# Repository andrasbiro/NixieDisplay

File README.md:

# Nixie Display

This is my modular nixie display/clock.

It is designed around modules. Each module has:

- 2 nixie tube (with decimal point)
- preceiding colon
- shift register based cathode driver circuit
- any number of modules can be cascaded together

With my boards, the cathode drivers are sandwitched behind the main boards,

The control is based around a Wemos D1 mini and a small 170V power supply. It can also dim the tubes via PWM controlled optogate switching off the high voltage from the tubes.

The recommended input voltage is between 7.5V and 12V.

## Hardware

The PCB design is the most problematic part of the project. I'm proud of the small outline of the NixieBoards, but other than that, they are full with problems. For more details see [its own readme](./hardware/electronics/README.md).

3d printed case coming soon.

## Firmware

The firmware is written in platformIO.

### NixieLib

The nixie driver is written in its own library, what I called NixieLib, and is fully documented in its header file. It supports the following input formats:

- 2 digit number + 4 boolean for the 4 dots (decimal and colon) for each module
- Integer, right adjusted across all modules
- Fixed point number (float input, number of decimals in another input)

### Clock application

The clock gets the current time from NTP, converts it to local time (CET/CEST, modify the winter/summer variables for your timezone) and displays ont the tubes.

It also has OTA enabled and telnet based debugging.

## Future developement

These are the modifications I plan:

- 3d printed case
- simplify NTP/timezone, use ESP's time.h instead of libs
- MQTT support, so it can display anything from my home assistant
- BH1750fvi based dimming
- second display, using Z570M tubes

Otherwise, grab it and modify it to your heart's content, but I probably won't. Pull requests are welcome!

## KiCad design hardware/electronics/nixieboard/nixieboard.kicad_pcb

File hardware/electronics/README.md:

# PCBs for nixie modules

These are the PCBs for the modular nixie display I designed, *but note that they
have many problems*. I'm a firmware engineer and I hate working on PCBs, and
even though these have many problems (and I autorouted most of them, which seems
sacrilege in hw design), it reached the point where it is good enough for me.

Pull requests are welcome.

## The Nixie board

The Nixie board is designed around IN-12B nixies with INS-1 neon bulbs as colon.
When the colon is not populated, the pads of it can be hidden in the preceding
board. Therefor, the board can be used both as clock displays with a colon and
numerical displays.

It will likely work with thin legged standing style tubes too (like the GDR,
like Z570M).

This board also has 4 M3 mounting holes, in each corner (on a 36.5x29mm
rectangle)

The anode resistors should be tuned for the tubes and anode voltage, here's what
I used for IN-12B / INS-1 at 170V power supply:

- R1/R3: 12kOhm (main anode resistor)
- R2/R4: 91kOhm (additional resistor on the decimal point's cathode)
- R5/R6: 240kOhm (INS-1 anode resistor)

### Known issues

- The board includes a WS2812B ("neopixel") backlight for each tube but that
  never worked. However, I never really wanted to use it, just thought about
  maybe if it looks good, so I won't fix it.
- When used with TPIC6592 drivers, INS-1 needs an extra ~50V zener in series to
  allow it turn off. Since it is not socketed, it can be easily added.

## The Driver boards

The driver board fits under the nixie board and provides power/control to it. I
have two versions of it:

- Based on HV5122 (in socket)
- Based on TPIC6592 (smd)

I highliy recommend the one based on TPIC6592, as HV5122 does not have a true
latch (only output enable) and way more expensive.

Both design has footprint for filter caps, but I never used it on the TPIC
design.

The module connecting pin headers are ~15mm from each other when the nixie board
is used without colon, but I ended up using wires on one side and 90 degree pin
headers on the other. The excess wire can be tugged away between the boards.

### Known issues

- The 15mm distance was designed for pin headers measured for 14mm distance, but
  what I got in the end was much closer
- The HV5122 board is not very well tested. It was an earlier iteration of the
  design, but with a few hw errors, I managed to blew my chips, and I don't
  intend to order new ones.

## The Control board

**The control board has the most issues, and I strongly recommend against
manufacturing it before fixing it. However, I did fix it with ugly hacks, so I
won't bother paying for another run. I put it here for archiving only.**

The control board is designed around a Wemos D1 mini (or clone) and a
cheap/small 170V power supply, both readily available from aliexpress and
similar sites. It also has a pin header for I2C, where I have a bh1750fvi light
sensor panel connected for dimming.

### Known issues

- I missed routing the 12V input to anything - fixable with a jumper wire
- AMS1117 was a bad decision for running the Wemos, and every other 5V device. I
  currently have a 3 pin DCDC board wired to its pads
- I used an optogate for dimming (via PWM) the high voltage. My driver board has
  a shutdown pin that would have probably work just as good
- The level shifters are configured for 12V (HV5122), and needs cutting a
  trace/adding a jumper wire to set it for 5V, needed for the TPIC drivers
- The power input needs bigger holes on the PCB to be able to use with proper
  wire gauge.

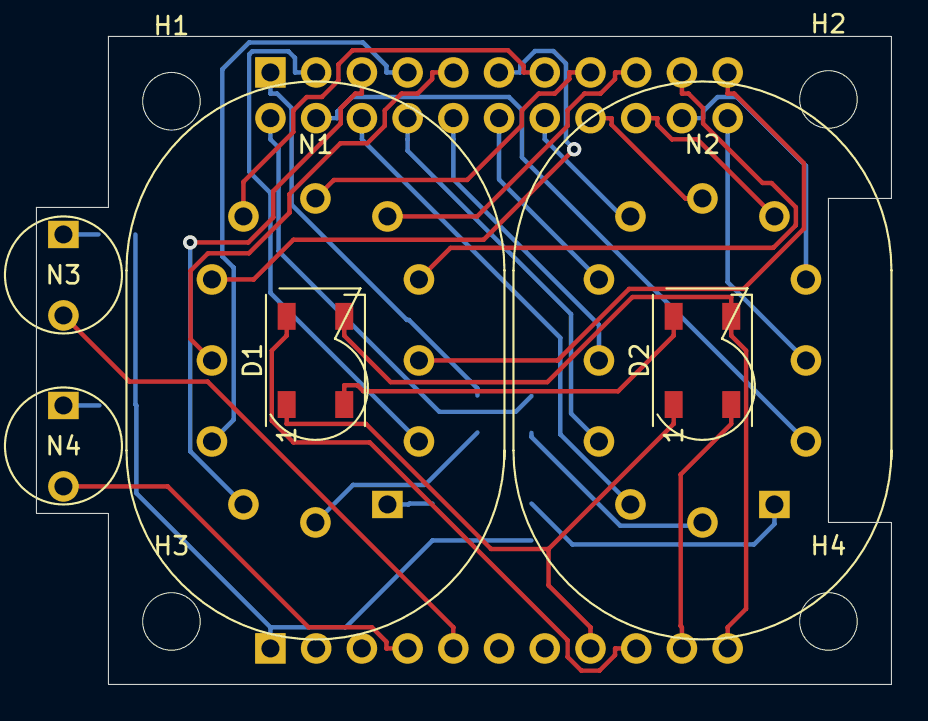
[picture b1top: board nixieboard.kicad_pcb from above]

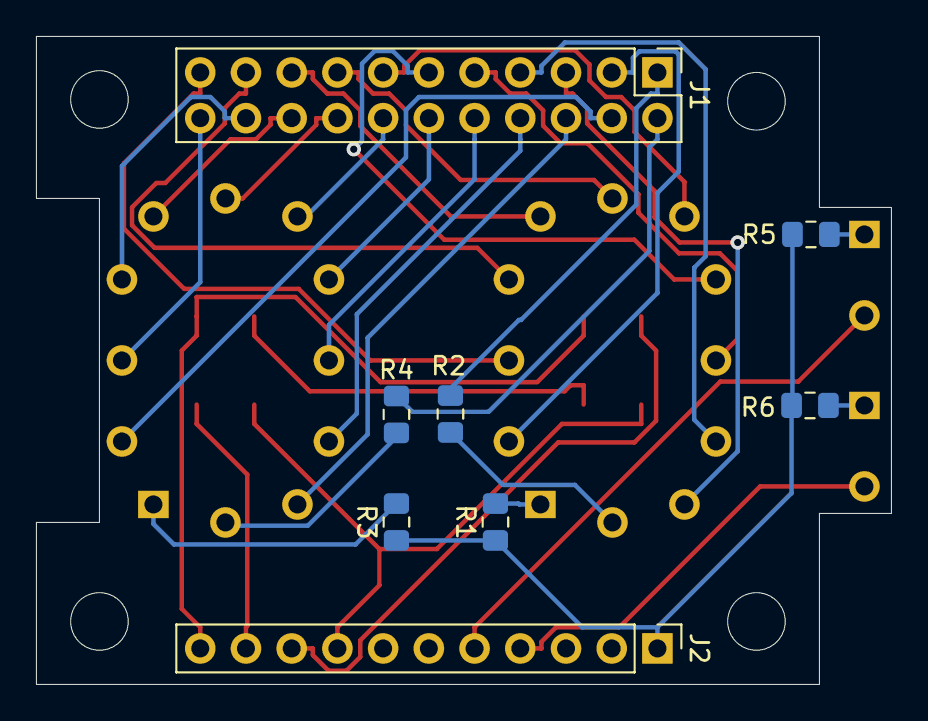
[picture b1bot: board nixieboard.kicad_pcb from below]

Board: 2 copper layers, 47.5 x 36.0 mm, 18 parts (8 on the bottom side), 36 nets.

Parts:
D1, D2: WS2812B; LED_WS2812B_PLCC4_5.0x5.0mm_P3.2mm
H1, H2, H3, H4: MountingHole; MountingHole_3.2mm_M3
J1: Cathodes; PinHeader_2x11_P2.54mm_Vertical
J2: PowerMisc; PinHeader_1x11_P2.54mm_Vertical
N1, N2: IN12B; in12b_pinsocket
N3, N4: INS-1; ins-1
R1, R3: 68k; R_0805_2012Metric_Pad1.15x1.40mm_HandSolder
R2, R4: 500k; R_0805_2012Metric_Pad1.15x1.40mm_HandSolder
R5, R6: 220k; R_0805_2012Metric_Pad1.15x1.40mm_HandSolder

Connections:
+5V: D1.1, D2.1, J2.8
GND: D1.3, D2.3, J2.11
HT: J2.1, R1.1, R3.1, R5.1, R6.1
unnamed: D1.2, D2.4
unnamed: D1.4, J2.9
unnamed: D2.2, J2.10
unnamed: J1.1, R2.2
unnamed: J1.2, R4.2
unnamed: J1.3, N1.2
unnamed: J1.4, N2.2
unnamed: J1.5, N1.11
unnamed: J1.6, N2.11
unnamed: J1.7, N1.10
unnamed: J1.8, N2.10
unnamed: J1.9, N1.9
unnamed: J1.10, N2.9
unnamed: J1.11, N1.8
unnamed: J1.12, N2.8
unnamed: J1.13, N1.7
unnamed: J1.14, N2.7
unnamed: J1.15, N1.6
unnamed: J1.16, N2.6
unnamed: J1.17, N1.5
unnamed: J1.18, N2.5
unnamed: J1.19, N1.4
unnamed: J1.20, N2.4
unnamed: J1.21, N1.3
unnamed: J1.22, N2.3
unnamed: J2.4, N4.2
unnamed: J2.5, N3.2
unnamed: N1.1, R1.2
unnamed: N1.12, R2.1
unnamed: N2.1, R3.2
unnamed: N2.12, R4.1
unnamed: N3.1, R5.2
unnamed: N4.1, R6.2

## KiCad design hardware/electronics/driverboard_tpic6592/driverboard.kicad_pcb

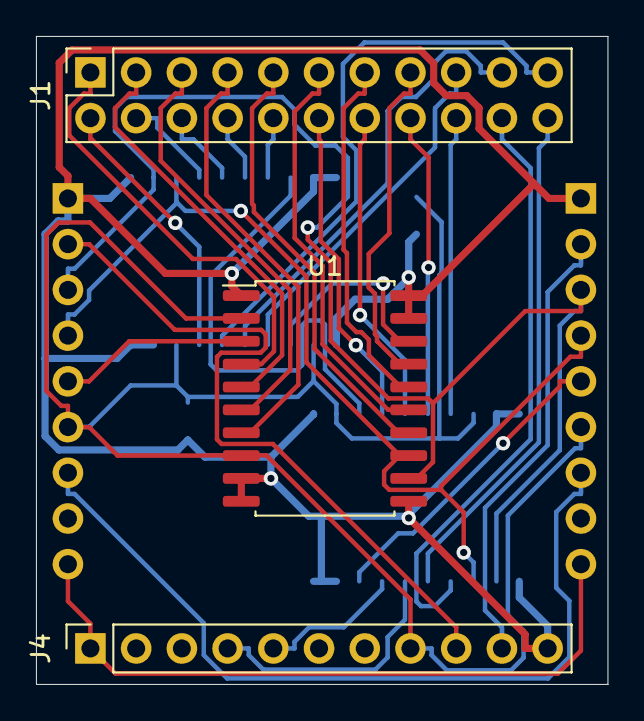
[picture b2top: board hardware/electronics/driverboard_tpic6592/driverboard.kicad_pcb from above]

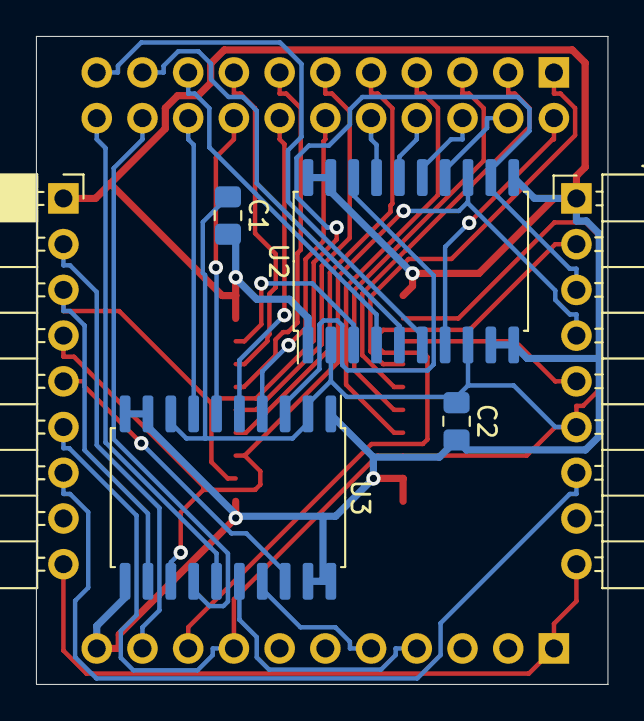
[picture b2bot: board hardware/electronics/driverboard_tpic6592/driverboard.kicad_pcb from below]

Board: 2 copper layers, 31.8 x 36.0 mm, 9 parts (6 on the bottom side), 36 nets.

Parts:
C1: C; C_0805_2012Metric_Pad1.18x1.45mm_HandSolder
C2: CP; C_0805_2012Metric_Pad1.18x1.45mm_HandSolder
J1: Cathodes; PinSocket_2x11_P2.54mm_Vertical
J2: In; PinHeader_1x09_P2.54mm_Horizontal
J3: Out; PinSocket_1x09_P2.54mm_Horizontal
J4: PowerMisc; PinSocket_1x11_P2.54mm_Vertical
U1, U2, U3: TPIC6595; SOIC-20W_7.5x12.8mm_P1.27mm

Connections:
+5V: C1.1, C2.1, J2.6, J3.6, J4.8, U1.2, U1.8, U2.2, U2.8, U3.2, U3.8
+12V: J2.7, J3.7
GND: C1.2, C2.2, J2.1, J3.1, J4.11, U1.1, U1.9, U1.10, U1.11, U1.19, U1.20, U2.1, U2.9, U2.10, U2.11, U2.19, U2.20, U3.1, U3.9, U3.10, U3.11, U3.19, U3.20
HT: J2.9, J3.9, J4.1
unnamed: J1.1, U1.4
unnamed: J1.2, U2.7
unnamed: J1.3, U1.5
unnamed: J1.4, U2.14
unnamed: J1.5, U1.6
unnamed: J1.6, U2.15
unnamed: J1.7, U1.7
unnamed: J1.8, U2.16
unnamed: J1.9, U1.14
unnamed: J1.10, U2.17
unnamed: J1.11, U1.15
unnamed: J1.12, U3.4
unnamed: J1.13, U1.16
unnamed: J1.14, U3.5
unnamed: J1.15, U1.17
unnamed: J1.16, U3.6
unnamed: J1.17, U2.4
unnamed: J1.18, U3.7
unnamed: J1.19, U2.5
unnamed: J1.20, U3.14
unnamed: J1.21, U2.6
unnamed: J1.22, U3.15
unnamed: J2.2, J4.9
unnamed: J2.3, J3.3, U1.12, U2.12, U3.12
unnamed: J2.4, J3.4, U1.13, U2.13, U3.13
unnamed: J2.5, U1.3
unnamed: J3.2, J4.10
unnamed: J3.5, U3.18
unnamed: J4.4, U3.16
unnamed: J4.5, U3.17
unnamed: U1.18, U2.3
unnamed: U2.18, U3.3

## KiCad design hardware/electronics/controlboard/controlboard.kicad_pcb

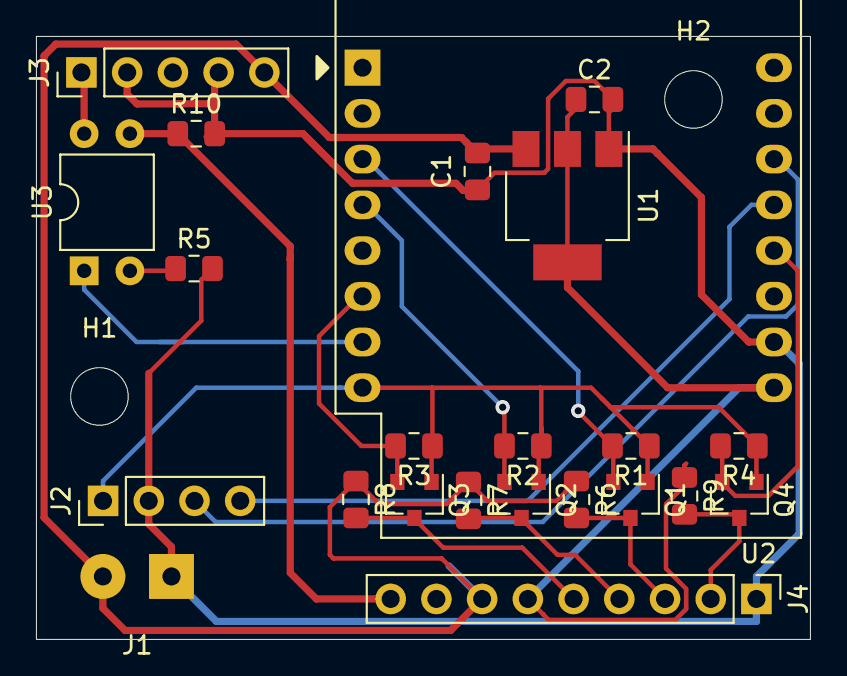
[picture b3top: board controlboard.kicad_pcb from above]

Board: 2 copper layers, 43.0 x 33.5 mm, 25 parts (0 on the bottom side), 18 nets.

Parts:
C1, C2: CP; C_0805_2012Metric_Pad1.15x1.40mm_HandSolder
H1, H2: MountingHole; MountingHole_3.2mm_M3_DIN965
J1: Power; SolderWirePad_1x02_P3.81mm_Drill1mm
J2: I2C; PinHeader_1x04_P2.54mm_Vertical
J3: HVmodule; PinHeader_1x05_P2.54mm_Vertical
J4: Control; PinHeader_1x09_P2.54mm_Vertical
Q1, Q2, Q3, Q4: BSS138; SOT-23
R1, R2, R3, R4, R6, R7, R8, R9: 10k; R_0805_2012Metric_Pad1.15x1.40mm_HandSolder
R5: 220; R_0805_2012Metric_Pad1.15x1.40mm_HandSolder
R10: 330k; R_0805_2012Metric_Pad1.15x1.40mm_HandSolder
U1: AMS1117-5.0; SOT-223-3_TabPin2
U2: WeMos_D1_mini; WEMOS_D1_mini_light
U3: TLP627; DIP-4_W7.62mm

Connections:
+3V3: J2.1, Q1.1, Q2.1, Q3.1, Q4.1, R1.1, R2.1, R3.1, R4.1, U2.8
+5V: C2.1, J4.6, R9.1, U1.2, U2.9
+12V: C1.1, J1.2, J3.5, J4.7, R6.1, R7.1, R8.1, U1.3
GND: C1.2, C2.2, J1.1, J2.2, J3.2, J3.4, J4.1, R5.2, R10.2, U1.1, U2.10
HT: J3.1, U3.4
unnamed: J2.3, U2.14
unnamed: J2.4, U2.13
unnamed: J4.2, Q4.3, R9.2
unnamed: J4.3, Q1.3, R6.2
unnamed: J4.4, Q2.3, R7.2
unnamed: J4.5, Q3.3, R8.2
unnamed: J4.9, R10.1, U3.3
unnamed: Q1.2, R1.2, U2.3
unnamed: Q2.2, R2.2, U2.4
unnamed: Q3.2, R3.2, U2.6
unnamed: Q4.2, R4.2, U2.12
unnamed: R5.1, U3.2
unnamed: U2.7, U3.1

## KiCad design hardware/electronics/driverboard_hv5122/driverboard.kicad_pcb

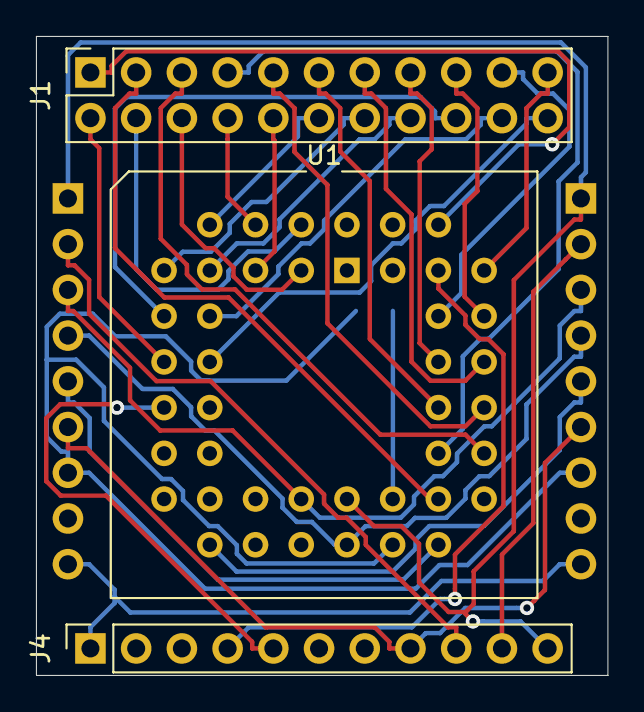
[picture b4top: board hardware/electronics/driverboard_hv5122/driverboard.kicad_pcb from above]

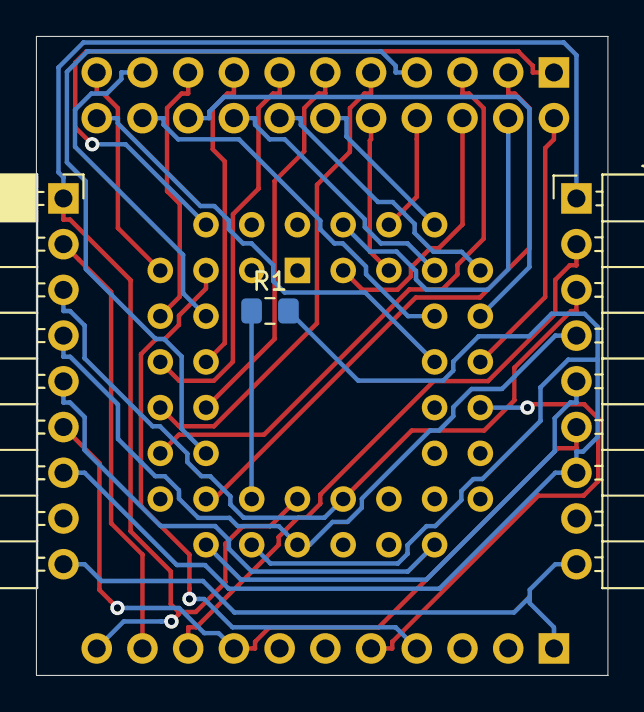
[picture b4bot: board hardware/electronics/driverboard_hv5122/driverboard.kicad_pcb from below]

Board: 2 copper layers, 31.8 x 35.5 mm, 6 parts (3 on the bottom side), 35 nets.

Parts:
J1: Cathodes; PinSocket_2x11_P2.54mm_Vertical
J2: In; PinHeader_1x09_P2.54mm_Horizontal
J3: Out; PinSocket_1x09_P2.54mm_Horizontal
J4: PowerMisc; PinSocket_1x11_P2.54mm_Vertical
R1: R; R_0805_2012Metric_Pad1.15x1.40mm_HandSolder
U1: HV5122_PLCC; PLCC-44_THT-Socket

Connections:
+5V: J2.6, J3.6, J4.8
+12V: J2.7, J3.7, R1.2, U1.26
GND: J2.1, J3.1, J4.11, U1.25
HT: J2.9, J3.9, J4.1
unnamed: J1.1, U1.40
unnamed: J1.2, U1.11
unnamed: J1.3, U1.30
unnamed: J1.4, U1.2
unnamed: J1.5, U1.31
unnamed: J1.6, U1.3
unnamed: J1.7, U1.32
unnamed: J1.8, U1.4
unnamed: J1.9, U1.33
unnamed: J1.10, U1.5
unnamed: J1.11, U1.34
unnamed: J1.12, U1.6
unnamed: J1.13, U1.35
unnamed: J1.14, U1.7
unnamed: J1.15, U1.36
unnamed: J1.16, U1.8
unnamed: J1.17, U1.37
unnamed: J1.18, U1.9
unnamed: J1.19, U1.38
unnamed: J1.20, U1.10
unnamed: J1.21, U1.39
unnamed: J1.22, U1.12
unnamed: J2.2, J4.9
unnamed: J2.3, J3.3, U1.23
unnamed: J2.4, J3.4, U1.24
unnamed: J2.5, U1.28
unnamed: J3.2, J4.10
unnamed: J3.5, U1.18
unnamed: J4.4, U1.41
unnamed: J4.5, U1.13
unnamed: R1.1, U1.27

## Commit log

2021-05-24 Initial commit of code
